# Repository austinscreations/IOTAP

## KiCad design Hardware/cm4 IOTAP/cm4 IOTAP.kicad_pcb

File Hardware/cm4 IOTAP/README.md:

kicad files
=====================

These kicad files are of the orginal design done by jon oxer.

I (austins_creations) got excited about a cm4 design. so put together this schematic
that should be all the needed elements to make the cm4 wifi IOT AP project work.
added the DIY POE switcher
added the ability for the cm4 to know which power mode is in use

pcb veiw is left mostly blank for jon to do routing on stream (if he so chooses to use the files)
but pcb veiw does have the elements from the last design copies over and converted for kicad use to ensure DRC passes

Credits
-------
 * Jonathan Oxer <jon@oxer.com.au>
 * Tony Smith
 * Austin's Creations <https://www.austinscreations.ca/>
 * All the folks watching and commenting on the streams!

License
-------
Copyright 2020-2022 SuperHouse Automation Pty Ltd  www.superhouse.tv  

The hardware portion of this project is licensed under the TAPR Open
Hardware License (www.tapr.org/OHL). The "license" folder within this
repository contains a copy of this license in plain text format.

The software portion of this project is licensed under the Simplified
BSD License. The "licence" folder within this project contains a
copy of this license in plain text format.

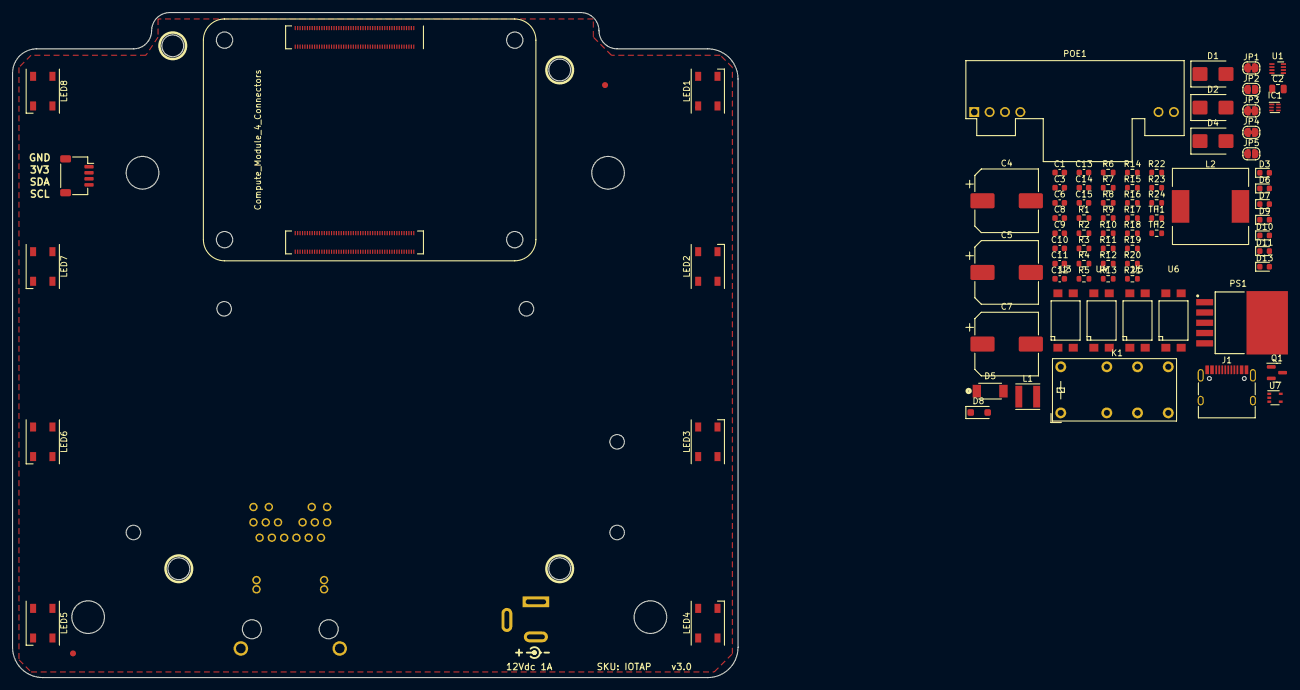
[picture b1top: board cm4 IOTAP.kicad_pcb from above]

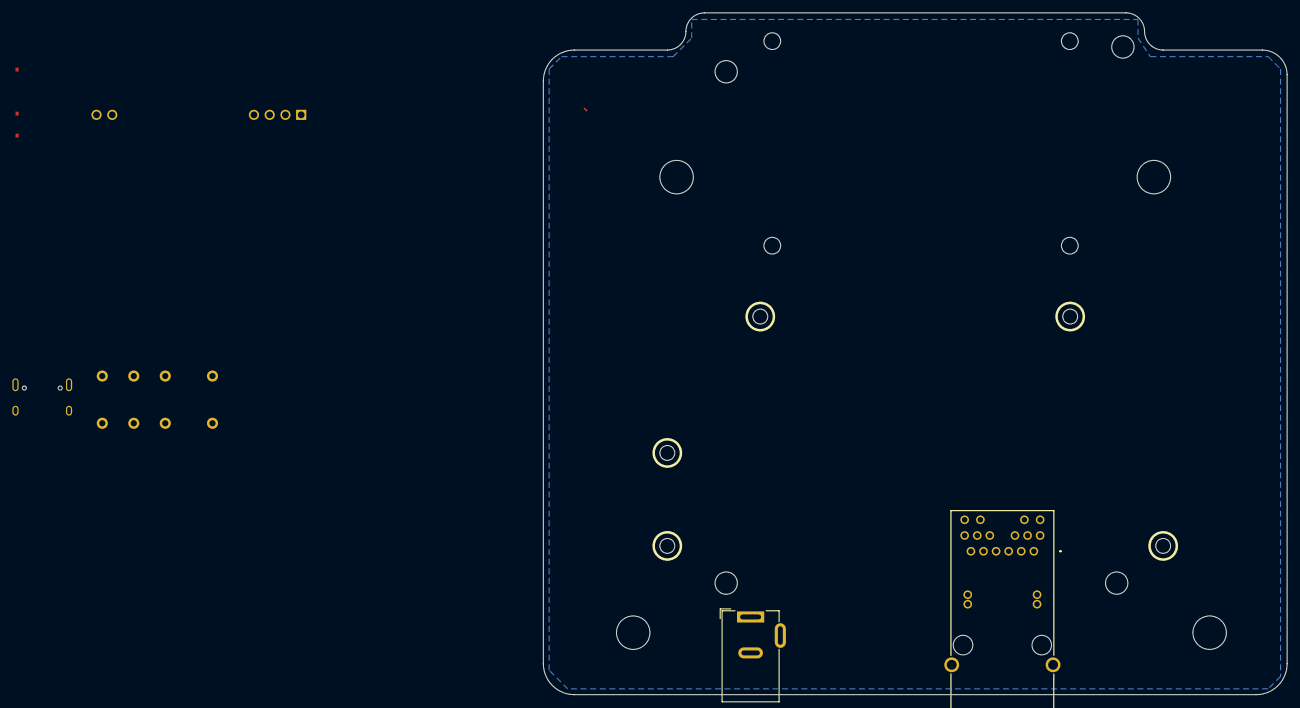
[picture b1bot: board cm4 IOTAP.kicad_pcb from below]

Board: 2 copper layers, 120.0 x 110.0 mm, 99 parts (2 on the bottom side), 72 nets.

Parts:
BJ1: Barrel_Jack; Barrel Jack
C1, C8, C9, C10, C11, C12, C13, C14, C15: 100nF; C_0603_1608Metric
C2: 1uf; C_0805_2012Metric
C3: 1uf; C_0603_1608Metric
C4, C5: 330uF 50v; CP_Elec_10x10
C6: 10uf; C_0603_1608Metric
C7: 330uF 25v; CP_Elec_10x10
D1, D2, D4: S3MB; D_SMB
D3, D10, D11: green; LED_0603_1608Metric
D5: PMEG4050EP; PMEG3050EP
D6, D9, D13: red; LED_0603_1608Metric
D7: blue; LED_0603_1608Metric
D8: SM4007; D_SOD-123F
FID1, FID2: Fiducial; Fiducial_1mm_Mask3mm
H1, H2, H3, H4, H5: MountingHole; MountingHole_2.5mm
H6, H7, H8, H9: MountingHole; MountingHole_3.5mm
H10, H11, H12, H13: MountingHole; MountingHole_5.3mm_M5
IC1: TPS3700-WSON; WSON-6_1.5x1.5mm_P0.5mm
J1: USB_C_Receptacle_USB2.0; USB_C_Receptacle_HRO_TYPE-C-31-M-12
JP1, JP3, JP4: Jumper_2_Bridged; SolderJumper-2_P1.3mm_Bridged_RoundedPad1.0x1.5mm
JP2: Jumper_2_Open; SolderJumper-2_P1.3mm_Open_RoundedPad1.0x1.5mm
JP5: USB OTG MODE; SolderJumper-2_P1.3mm_Open_RoundedPad1.0x1.5mm
K1: J104D2C3VDC.15S; Relay_DPDT_Finder_30.22
L1: 33UH; L_Vishay_IFSC-1515AH_4x4x1.8mm
L2: 33UH; 12x12x8 inductor
LED1, LED2, LED3, LED4, LED5, LED6, LED7, LED8: SK6812; LED_SK6812_PLCC4_5.0x5.0mm_P3.2mm
POE1: DP1435
PS1: LM2596S-5.0; LM2596S
Q1: AO3400A; SOT-23
Qw1: qwiic_horizontal; qwiic horizontal
R1, R2, R3, R8, R12, R13, R14, R16, R17, R18, R19: 10k; R_0603_1608Metric
R4: 2M; R_0603_1608Metric
R5: 62k; R_0603_1608Metric
R6: 22k; R_0603_1608Metric
R7, R9, R10, R15: 4.7k; R_0603_1608Metric
R11, R23, R24: 470r; R_0603_1608Metric
R20, R22: 2.2k; R_0603_1608Metric
R21: 1k; R_0603_1608Metric
RJ45_1: ARJ-139; ARJ139
TH1, TH2: 16v 500mA PTC; R_0603_1608Metric
U1: MAX15062A; DFN-8_2x2mm_P0.5mm
U2: Compute_Module_4_Connectors; Raspberry-Pi-4-Compute-Module
U3, U4, U5, U6: PC817; smd4
U7: 74LVC1G07SE-7; SOT-353_SC-70-5

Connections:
2.1mm_SIG: BJ1.1, D2.1 (K), D10.2 (A), R12.2
+1V8: JP2.1 (A), TH1.1
+3.3V: D9.2 (A), D13.2 (A), JP1.1 (A), Qw1.2 (VCC), R16.1, R17.1, R18.1, R19.1, RJ45_1.18 (A_YELLOW), RJ45_1.20 (K_ORANGE/A_GREEN), TH2.1, U7.5 (VCC)
+3.3VA: C6.1, D7.2 (A), D8.1 (K), IC1.2 (VDD), L1.2, R8.1, R15.2, U1.4 (FB/Vout)
+5V: C7.1, C8.2, C9.2, C10.2, C11.2, C12.2, C13.2, C14.2, C15.2, D6.2 (A), L2.2, LED1.3 (VDD), LED2.3 (VDD), LED3.3 (VDD), LED4.3 (VDD), LED5.3 (VDD), LED6.3 (VDD), LED7.3 (VDD), LED8.3 (VDD), PS1.4 (FB), U2.77 (+5V), U2.79 (+5V), U2.81 (+5V), U2.83 (+5V), U2.85 (+5V), U2.87 (+5V)
+12V: C4.1, C5.1, D1.2 (A), D2.2 (A), D4.2 (A), PS1.1 (VIN)
/nPWR_LED: U2.95 (~PI_LED_nPWR), U7.2
DIY_SIG: D8.2 (A), JP4.2 (B), Q1.3 (D), U6.2
ETH_LEDG: R24.2, U2.17 (~Ethernet_nLED2)
ETH_LEDY: R23.2, U2.15 (~Ethernet_nLED3)
GND: BJ1.2, BJ1.3, C1.2, C4.2, C5.2, C7.2, C8.1, C9.1, C10.1, C11.1, C12.1, C13.1, C14.1, C15.1, D5.2 (A), J1.A1 (GND), J1.A12 (GND), J1.B1 (GND), J1.B12 (GND), J1.S1 (SHIELD), JP3.2 (B), LED1.1 (VSS), LED2.1 (VSS), LED3.1 (VSS), LED4.1 (VSS), LED5.1 (VSS), LED6.1 (VSS), LED7.1 (VSS), LED8.1 (VSS), POE1.GND, PS1.3 (GND), PS1.5 (~ON/OFF), Qw1.1 (GND), Qw1.MP, R22.1, RJ45_1.MH1, RJ45_1.MH2, U2.1 (GND), U2.2 (GND), U2.7 (GND), U2.8 (GND), U2.13 (GND), U2.14 (GND), U2.22 (GND), U2.23 (GND), U2.32 (GND), U2.33 (GND), U2.42 (GND), U2.43 (GND), U2.52 (GND), U2.53 (GND), U2.59 (GND), U2.60 (GND), U2.65 (GND), U2.66 (GND), U2.71 (GND), U2.74 (GND), U2.98 (GND), U2.107 (GND), U2.108 (GND), U2.113 (GND), U2.114 (GND), U2.119 (GND), U2.120 (GND), U2.125 (GND), U2.126 (GND), U2.131 (GND), U2.132 (GND), U2.137 (GND), U2.138 (GND), U2.144 (GND), U2.150 (GND), U2.155 (GND), U2.156 (GND), U2.161 (GND), U2.162 (GND), U2.167 (GND), U2.168 (GND), U2.173 (GND), U2.174 (GND), U2.179 (GND), U2.180 (GND), U2.185 (GND), U2.186 (GND), U2.191 (GND), U2.192 (GND), U2.197 (GND), U2.198 (GND), U3.2, U3.3, U4.2, U4.3, U5.2, U5.3, U6.3, U7.3 (GND)
GPIO8: R16.2, U2.39 (GPIO8), U3.4
GPIO18: R11.1, U2.49 (GPIO18)
GPIO23: R19.2, U2.47 (GPIO23), U6.4
GPIO24: R18.2, U2.45 (GPIO24), U5.4
GPIO25: R17.2, U2.41 (GPIO25), U4.4
GPIO_VREF: JP1.2 (B), JP2.2 (B), U2.78 (GPIO_VREF)
unnamed: D3.1 (K), R2.1
unnamed: D5.1 (K), L2.1, PS1.2 (OUT)
unnamed: D6.1 (K), R7.1
unnamed: D7.1 (K), R10.1
unnamed: D9.1 (K), R9.1
unnamed: D10.1 (K), R1.1
unnamed: D11.1 (K), R3.1
unnamed: D13.1 (K), R21.1
unnamed: IC1.4 (INA+), R4.2, R5.1
unnamed: IC1.3 (INB-), R5.2, R6.1
unnamed: IC1.1 (OUTB), IC1.6 (OUTA), Q1.1 (G), R8.2
unnamed: JP3.1 (A), R1.2, R2.2, R3.2, R7.2
unnamed: JP4.1 (A), R10.2
unnamed: JP5.1 (A), R20.1
unnamed: J1.A4 (VBUS), J1.A9 (VBUS), J1.B4 (VBUS), J1.B9 (VBUS), JP5.2 (B)
unnamed: LED1.2 (DIN), R11.2
unnamed: LED1.4 (DOUT), LED2.2 (DIN)
unnamed: LED2.4 (DOUT), LED3.2 (DIN)
unnamed: LED3.4 (DOUT), LED4.2 (DIN)
unnamed: LED4.4 (DOUT), LED5.2 (DIN)
unnamed: LED5.4 (DOUT), LED6.2 (DIN)
unnamed: LED6.4 (DOUT), LED7.2 (DIN)
unnamed: LED7.4 (DOUT), LED8.2 (DIN)
unnamed: R12.1, U3.1
unnamed: R13.1, U4.1
unnamed: R14.1, U5.1
unnamed: R15.1, U6.1
unnamed: R21.2, U7.4
unnamed: C1.1, RJ45_1.1 (CT_1), RJ45_1.6 (CT_2), RJ45_1.7 (CT_3), RJ45_1.12 (CT_4)
unnamed: R24.1, RJ45_1.19 (K_GREEN/A_ORANGE)
unnamed: R23.1, RJ45_1.17 (K_YELLOW)
unnamed: TH1.2, U2.88 (CM4_1.8V_Out), U2.90 (CM4_1.8V_Out)
unnamed: TH2.2, U2.84 (CM4_3.3V_Out), U2.86 (CM4_3.3V_Out)
unnamed: L1.1, U1.8 (LX)
unnamed: C3.1, U1.3 (VCC)
unnamed: R9.2, U2.21 (~Pi_nLED_Activity)
PASSIVE_SIG: D1.1 (K), D11.2 (A), R14.2
POE_SIG: D3.2 (A), D4.1 (K), POE1.VOUT, R13.2
SCL0: Qw1.4 (SCL), U2.80 (I2C_SCL0)
SDA0: Qw1.3 (SDA), U2.82 (I2C_SDA0)
USB2_N: J1.A7 (D-), J1.B7 (D-), U2.103 (USB_N)
USB2_P: J1.A6 (D+), J1.B6 (D+), U2.105 (USB_P)
USBOTG: R20.2, R22.2, U2.101 (USB_OTG_ID)
VA1: POE1.VA1, RJ45_1.13 (POE_1)
VA2: POE1.VA2, RJ45_1.14 (POE_2)
VB1: C2.1, R4.1, RJ45_1.15 (POE_3), U1.1 (VIN), U1.2 (EN/UVLO)
VB2: C2.2, C3.2, C6.2, IC1.5 (GND), Q1.2 (S), R6.2, RJ45_1.16 (POE_4), U1.5 (MODE), U1.7 (GND)
ethPair0_N: RJ45_1.10 (TRD0-), U2.10 (Ethernet_Pair0_N)
ethPair0_P: RJ45_1.11 (TRD0+), U2.12 (Ethernet_Pair0_P)
ethPair1_N: RJ45_1.5 (TRD1-), U2.6 (Ethernet_Pair1_N)
ethPair1_P: RJ45_1.4 (TRD1+), U2.4 (Ethernet_Pair1_P)
ethPair2_N: RJ45_1.2 (TRD2-), U2.9 (Ethernet_Pair2_N)
ethPair2_P: RJ45_1.3 (TRD2+), U2.11 (Ethernet_Pair2_P)
ethPair3_N: RJ45_1.9 (TRD3-), U2.5 (Ethernet_Pair3_N)
ethPair3_P: RJ45_1.8 (TRD3+), U2.3 (Ethernet_Pair3_P)

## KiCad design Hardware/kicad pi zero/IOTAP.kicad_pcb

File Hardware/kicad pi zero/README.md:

kicad files
=====================

These kicad files are of the orginal design done by jon oxer.

I (austins_creations) imported these to kicad to get the general pcb layout for a CM4 design

Credits
-------
 * Jonathan Oxer <jon@oxer.com.au>
 * Tony Smith
 * Austin's Creations <https://www.austinscreations.ca/>
 * All the folks watching and commenting on the streams!

License
-------
Copyright 2020-2022 SuperHouse Automation Pty Ltd  www.superhouse.tv  

The hardware portion of this project is licensed under the TAPR Open
Hardware License (www.tapr.org/OHL). The "license" folder within this
repository contains a copy of this license in plain text format.

The software portion of this project is licensed under the Simplified
BSD License. The "licence" folder within this project contains a
copy of this license in plain text format.

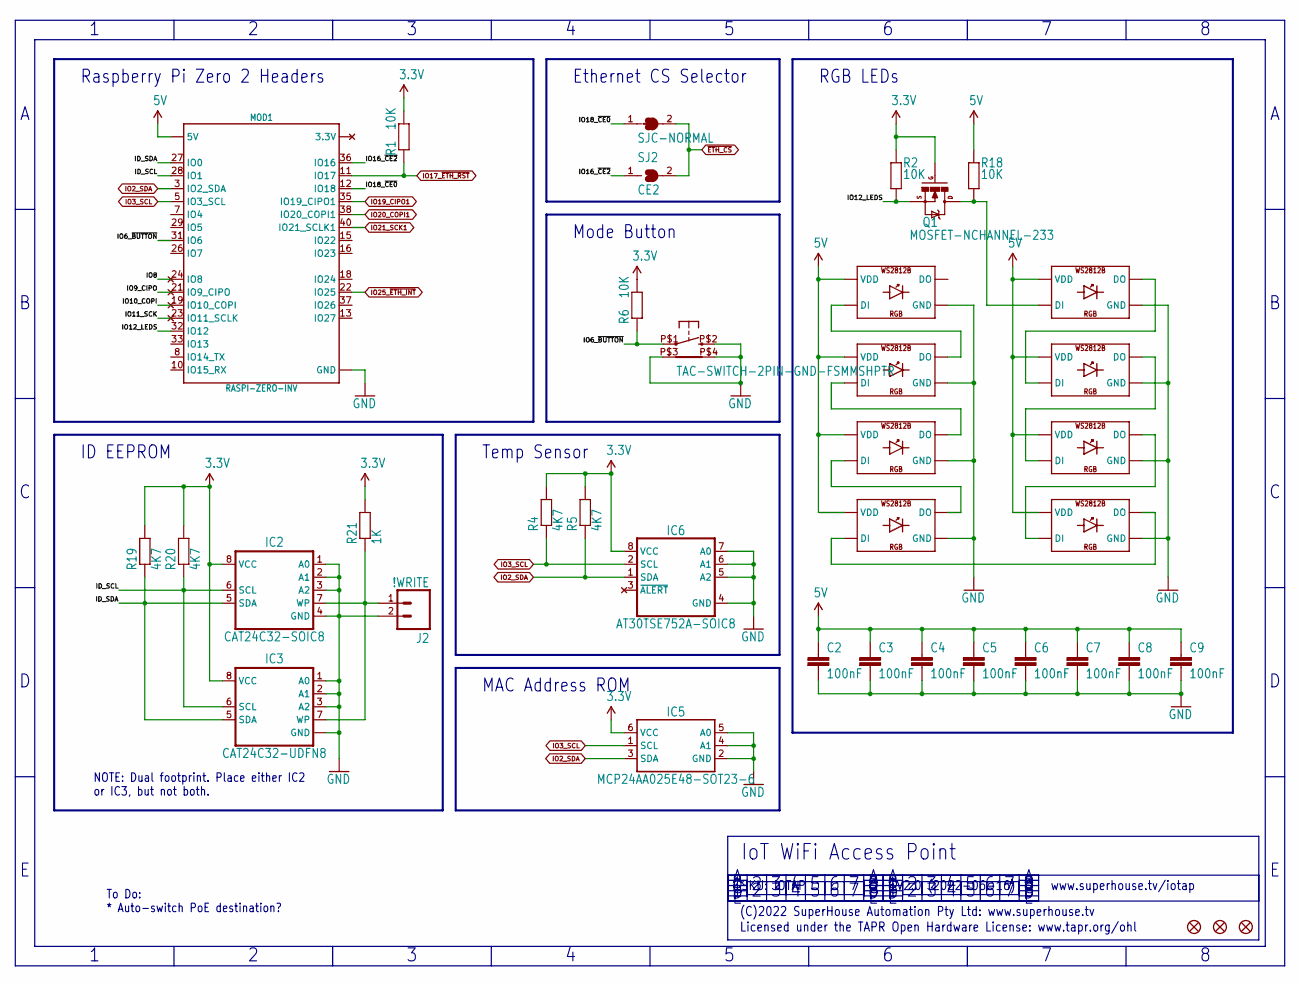
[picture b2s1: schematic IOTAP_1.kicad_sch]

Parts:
C2, C3, C4, C5, C6, C7, C8, C9: 100nF; C0603
FID1, FID2, FID3: FIDUCIAL1X2.5; FIDUCIAL-1X2.5
IC2: CAT24C32-SOIC8; SOIC8
IC3: CAT24C32-UDFN8; UDFN8
IC5: MCP24AA025E48-SOT23-6; SOT23-6
IC6: AT30TSE752A-SOIC8; SOIC8
J2: !WRITE; 1X02
LED1, LED2, LED3, LED4, LED5, LED6, LED7, LED8: WS2812B5050; WS2812B
MOD1: RASPI-ZERO-INV; RPI-ZERO-INV
Q1: MOSFET-NCHANNEL-233; SOT23-3
R1, R2, R6, R18: 10K; R0603
R4, R5, R19, R20: 4K7; R0603
R21: 1K; R0603
SJ1: SJC-NORMAL; SJC
SJ2: CE2; SJ
SW1: TAC-SWITCH-2PIN-GND-FSMMSHPTR; TC-120V

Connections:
3.3V: IC2.8 (VCC), IC3.8 (VCC), IC5.6 (VCC), IC6.8 (VCC), Q1.1 (G), R1.2, R2.2, R4.2, R5.2, R6.2, R19.2, R20.2, R21.2; also elsewhere on the board
5V: C2.1, C3.1, C4.1, C5.1, C6.1, C7.1, C8.1, C9.1, LED1.1-VDD (VDD), LED2.1-VDD (VDD), LED3.1-VDD (VDD), LED4.1-VDD (VDD), LED5.1-VDD (VDD), LED6.1-VDD (VDD), LED7.1-VDD (VDD), LED8.1-VDD (VDD), MOD1.2 (5V), MOD1.4 (5V), R18.2; also elsewhere on the board
GND: C2.2, C3.2, C4.2, C5.2, C6.2, C7.2, C8.2, C9.2, IC2.1 (A0), IC2.2 (A1), IC2.3 (A2), IC2.4 (GND), IC3.1 (A0), IC3.2 (A1), IC3.3 (A2), IC3.4 (GND), IC3.PAD (GND), IC5.2 (GND), IC5.4 (A1), IC5.5 (A0), IC6.4 (GND), IC6.5 (A2), IC6.6 (A1), IC6.7 (A0), J2.2, LED1.3-GND (GND), LED2.3-GND (GND), LED3.3-GND (GND), LED4.3-GND (GND), LED5.3-GND (GND), LED6.3-GND (GND), LED7.3-GND (GND), LED8.3-GND (GND), MOD1.6 (GND), MOD1.9 (GND), MOD1.14 (GND), MOD1.20 (GND), MOD1.25 (GND), MOD1.30 (GND), MOD1.34 (GND), MOD1.39 (GND), SW1.P$2 (2), SW1.P$3 (TAB1), SW1.P$4 (TAB2); also elsewhere on the board
ID_SCL: IC2.6 (SCL), IC3.6 (SCL), MOD1.28 (IO1), R20.1
ID_SDA: IC2.5 (SDA), IC3.5 (SDA), MOD1.27 (IO0), R19.1
IO2_SDA: IC5.3 (SDA), IC6.1 (SDA), MOD1.3 (IO2_SDA), R5.1; also elsewhere on the board
IO3_SCL: IC5.1 (SCL), IC6.2 (SCL), MOD1.5 (IO3_SCL), R4.1; also elsewhere on the board
IO6_~BUTTON: MOD1.31 (IO6), R6.1, SW1.P$1 (1)
IO8: MOD1.24 (IO8)
IO9_CIPO: MOD1.21 (IO9_CIPO)
IO10_COPI: MOD1.19 (IO10_COPI)
IO11_SCK: MOD1.23 (IO11_SCLK)
IO12_LEDS: MOD1.32 (IO12), Q1.2 (S), R2.1
IO16_~CE2: MOD1.36 (IO16), SJ2.1
IO17_~ETH_RST: MOD1.11 (IO17), R1.1; also elsewhere on the board
IO18_~CE0: MOD1.12 (IO18), SJ1.1
IO19_CIPO1: MOD1.35 (IO19_CIPO1); also elsewhere on the board
IO20_COPI1: MOD1.38 (IO20_COPI1); also elsewhere on the board
IO21_SCK1: MOD1.40 (IO21_SCLK1); also elsewhere on the board
IO25_~ETH_INT: MOD1.22 (IO25); also elsewhere on the board
LEDS: LED1.4-DIN (DI), Q1.3 (D), R18.1
unnamed: IC2.7 (WP), IC3.7 (WP), J2.1, R21.1
unnamed: LED4.2-DOUT (DO), LED5.4-DIN (DI)
unnamed: LED5.2-DOUT (DO), LED6.4-DIN (DI)
unnamed: LED6.2-DOUT (DO), LED7.4-DIN (DI)
unnamed: LED7.2-DOUT (DO), LED8.4-DIN (DI)
unnamed: LED1.2-DOUT (DO), LED2.4-DIN (DI)
unnamed: LED2.2-DOUT (DO), LED3.4-DIN (DI)
unnamed: LED3.2-DOUT (DO), LED4.4-DIN (DI)
~ETH_CS: SJ1.2, SJ2.2; also elsewhere on the board

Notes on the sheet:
RGB LEDs
ID EEPROM
(C)2022 SuperHouse Automation Pty Ltd: www.superhouse.tv
MAC Address ROM
SKU: IOTAP
NOTE: Dual footprint. Place either IC2 or IC3, but not both.
To Do: * Auto-switch PoE destination?
Temp Sensor
Licensed under the TAPR Open Hardware License: www.tapr.org/ohl
Mode Button
Ethernet CS Selector
IoT WiFi Access Point
www.superhouse.tv/iotap
V2.0 (2022-06-16)
Raspberry Pi Zero 2 Headers

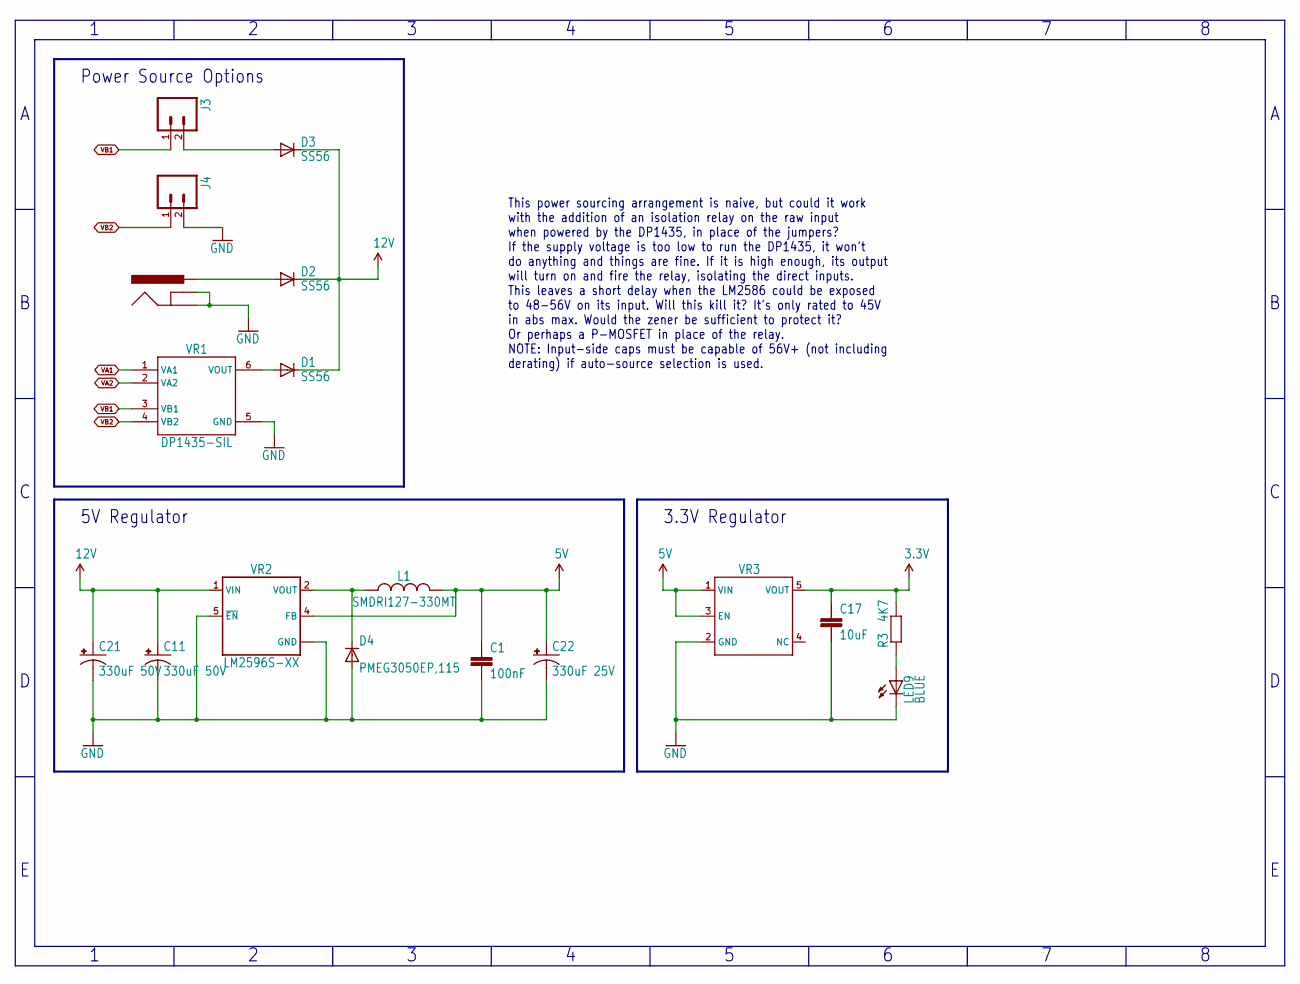
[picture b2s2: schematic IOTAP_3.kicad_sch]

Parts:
C1: 100nF; C0603
C11, C21: 330uF 50V; PANASONIC_G
C17: 10uF; C0805
C22: 330uF 25V; PANASONIC_G
D1, D2, D3: SS56; SMA-DIODE
D4: PMEG3050EP,115; SOD-128
J1: POWER_JACK-SLOTS; POWER_JACK_SLOTS
J3, J4: M02-PIN-RA; 1X02-P-RA
L1: SMDRI127-330MT; INDPM120120X800N
LED9: BLUE; LED-0603
R3: 4K7; R0603
VR1: DP1435-SIL; DP1435
VR2: LM2596S-XX; TO170P1435X465-6N
VR3: AP2112KSOT25; SOT23-5

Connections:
3.3V: C17.1, R3.2, VR3.5 (VOUT); also elsewhere on the board
5V: C1.1, C22.+, L1.2, VR2.4 (FB), VR3.1 (VIN), VR3.3 (EN); also elsewhere on the board
12V: C11.+, C21.+, D1.C, D2.C, D3.C, VR2.1 (VIN)
GND: C1.2, C11.-, C17.2, C21.-, C22.-, D4.2 (A), J1.GND, J1.GNDBREAK, J4.2, LED9.C, VR1.5 (GND), VR2.3 (GND), VR2.5 (~EN), VR2.6 (GND), VR3.2 (GND); also elsewhere on the board
unnamed: D3.A, J3.2
unnamed: D4.1 (C), L1.1, VR2.2 (VOUT)
unnamed: LED9.A, R3.1
unnamed: D2.A, J1.PWR
unnamed: D1.A, VR1.6 (VOUT)
VA1: VR1.1 (VA1); also elsewhere on the board
VA2: VR1.2 (VA2); also elsewhere on the board
VB1: J3.1, VR1.3 (VB1); also elsewhere on the board
VB2: J4.1, VR1.4 (VB2); also elsewhere on the board

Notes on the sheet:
This power sourcing arrangement is naive, but could it work with the addition of an isolation relay on the raw input when powered by the DP1435, in place of the jumpers? If the supply voltage is too low to run the DP1435, it won't do anything and things are fine. If it is high enough, its output wi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
5V Regulator
Power Source Options
3.3V Regulator

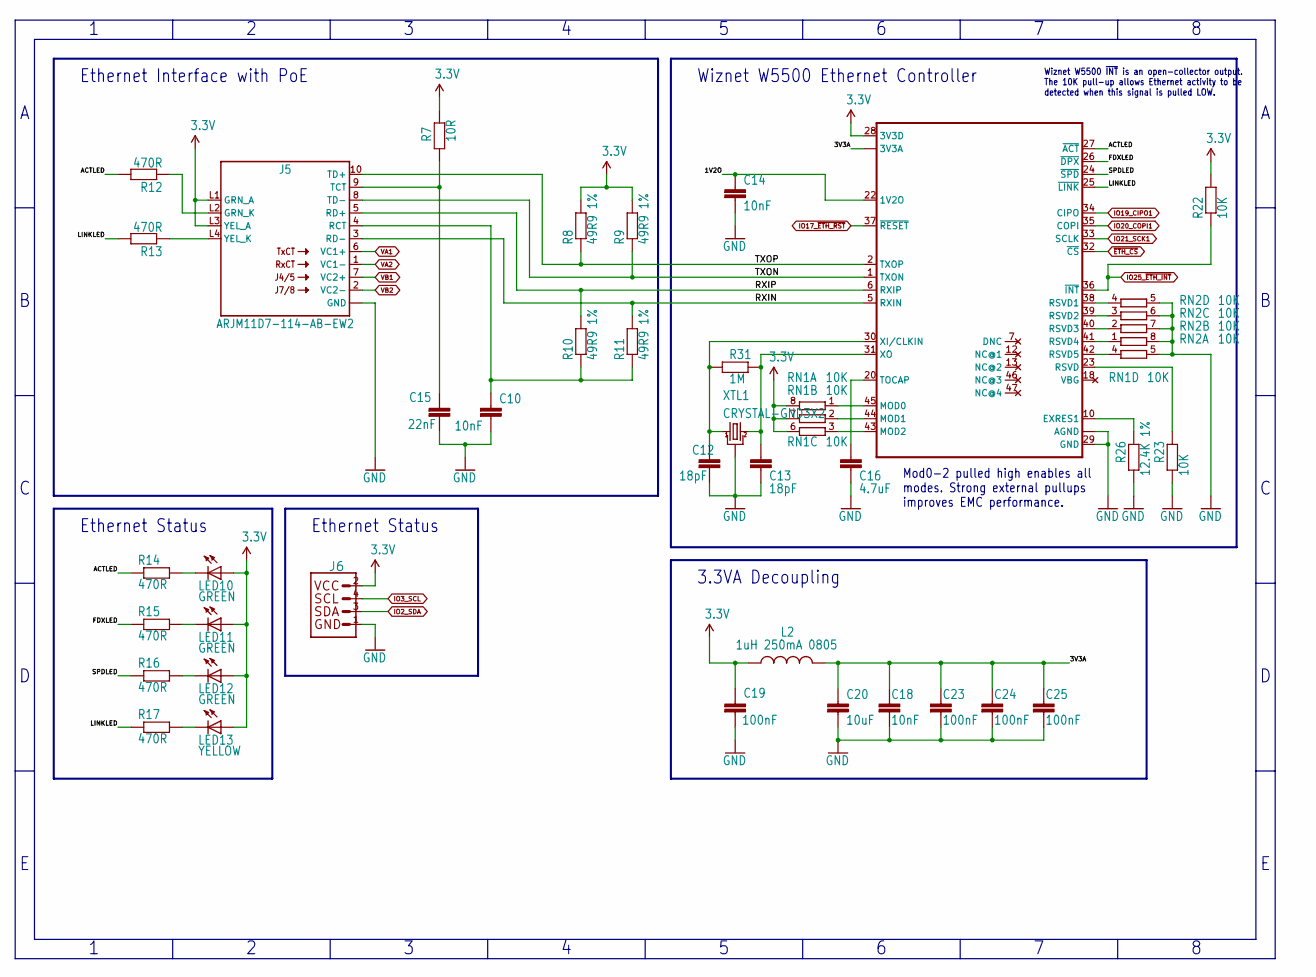
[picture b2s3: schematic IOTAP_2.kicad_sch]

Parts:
C10, C14, C18: 10nF; C0603
C12, C13: 18pF; C0603
C15: 22nF; C0603
C16: 4.7uF; C0603
C19, C23, C24, C25: 100nF; C0603
C20: 10uF; C0805
IC4: W5500-LQFP; LQFP48
J5: ARJM11D7-114-AB-EW2; ARJM11D7114ABEW2
J6: QWIICJS-1MM; 1X04_QWIIC_1MM_RA
L2: 1uH 250mA 0805; L2012C
LED10, LED11, LED12: GREEN; LED-0603
LED13: YELLOW; LED-0603
R7: 10R; R0603
R8, R9, R10, R11: 49R9 1%; R0603
R12, R13, R14, R15, R16, R17: 470R; R0603
R22, R23: 10K; R0603
R26: 12.4K 1%; R0603
R31: 1M; R0603
RN1, RN2: 10K; CAY16
XTL1: CRYSTAL-GND3X2; CRYSTAL-SMD-3X2

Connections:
1V2O: C14.1, IC4.22 (1V2O)
3.3V: C19.1, IC4.28 (3V3D), J5.L1 (GRN_A), J5.L3 (YEL_A), J6.2, L2.1, LED10.A, LED11.A, LED12.A, LED13.A, R7.1, R8.2, R9.2, R22.2, RN1.6 (2), RN1.7 (2), RN1.8 (2); also elsewhere on the board
3V3A: C18.1, C20.1, C23.1, C24.1, C25.1, IC4.4 (3V3A), IC4.8 (3V3A), IC4.11 (3V3A), IC4.15 (3V3A), IC4.17 (3V3A), IC4.21 (3V3A), L2.2
ACTLED: IC4.27 (~ACT), R12.2, R14.1
FDXLED: IC4.26 (~DPX), R15.1
GND: C10.2, C12.2, C13.2, C14.2, C15.2, C16.2, C18.2, C19.2, C20.2, C23.2, C24.2, C25.2, IC4.3 (AGND), IC4.9 (AGND), IC4.14 (AGND), IC4.16 (AGND), IC4.19 (AGND), IC4.29 (GND), IC4.48 (AGND), J5.MH1 (GND), J5.MH2 (GND), J6.1, R23.2, R26.2, RN1.5 (2), RN2.5 (2), RN2.6 (2), RN2.7 (2), RN2.8 (2), XTL1.2 (GND), XTL1.4 (GND); also elsewhere on the board
IO2_SDA: J6.3; also elsewhere on the board
IO3_SCL: J6.4; also elsewhere on the board
IO17_~ETH_RST: IC4.37 (~RESET); also elsewhere on the board
IO19_CIPO1: IC4.34 (CIPO); also elsewhere on the board
IO20_COPI1: IC4.35 (COPI); also elsewhere on the board
IO21_SCK1: IC4.33 (SCLK); also elsewhere on the board
IO25_~ETH_INT: IC4.36 (~INT), R22.1; also elsewhere on the board
LINKLED: IC4.25 (~LINK), R13.2, R17.1
unnamed: J5.L4 (YEL_K), R13.1
unnamed: J5.L2 (GRN_K), R12.1
unnamed: C13.1, IC4.31 (XO), R31.1, XTL1.3 (2)
unnamed: C10.1, J5.4 (RCT), R10.1, R11.1
unnamed: LED12.C, R16.2
unnamed: C12.1, IC4.30 (XI/CLKIN), R31.2, XTL1.1
unnamed: LED13.C, R17.2
unnamed: C16.1, IC4.20 (TOCAP)
unnamed: C15.1, J5.9 (TCT), R7.2
unnamed: IC4.10 (EXRES1), R26.1
unnamed: IC4.23 (RSVD), R23.1
unnamed: IC4.45 (MOD0), RN1.1
unnamed: IC4.44 (MOD1), RN1.2 (1)
unnamed: IC4.43 (MOD2), RN1.3 (1)
unnamed: IC4.42 (RSVD5), RN1.4 (1)
unnamed: IC4.41 (RSVD4), RN2.1
unnamed: IC4.40 (RSVD3), RN2.2 (1)
unnamed: IC4.39 (RSVD2), RN2.3 (1)
unnamed: IC4.38 (RSVD1), RN2.4 (1)
unnamed: LED11.C, R15.2
unnamed: LED10.C, R14.2
RXIN: IC4.5 (RXIN), J5.3 (RD-), R11.2
RXIP: IC4.6 (RXIP), J5.5 (RD+), R10.2
SPDLED: IC4.24 (~SPD), R16.1
TXON: IC4.1 (TXON), J5.8 (TD-), R9.1
TXOP: IC4.2 (TXOP), J5.10 (TD+), R8.1
VA1: J5.6 (VC1+); also elsewhere on the board
VA2: J5.1 (VC1-); also elsewhere on the board
VB1: J5.7 (VC2+); also elsewhere on the board
VB2: J5.2 (VC2-); also elsewhere on the board
~ETH_CS: IC4.32 (~CS); also elsewhere on the board

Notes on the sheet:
Ethernet Interface with PoE
3.3VA Decoupling
Ethernet Status
Wiznet W5500 ~{INT} is an open-collector output. The 10K pull-up allows Ethernet activity to be detected when this signal is pulled LOW.
Mod0-2 pulled high enables all modes. Strong external pullups improves EMC performance.
Wiznet W5500 Ethernet Controller

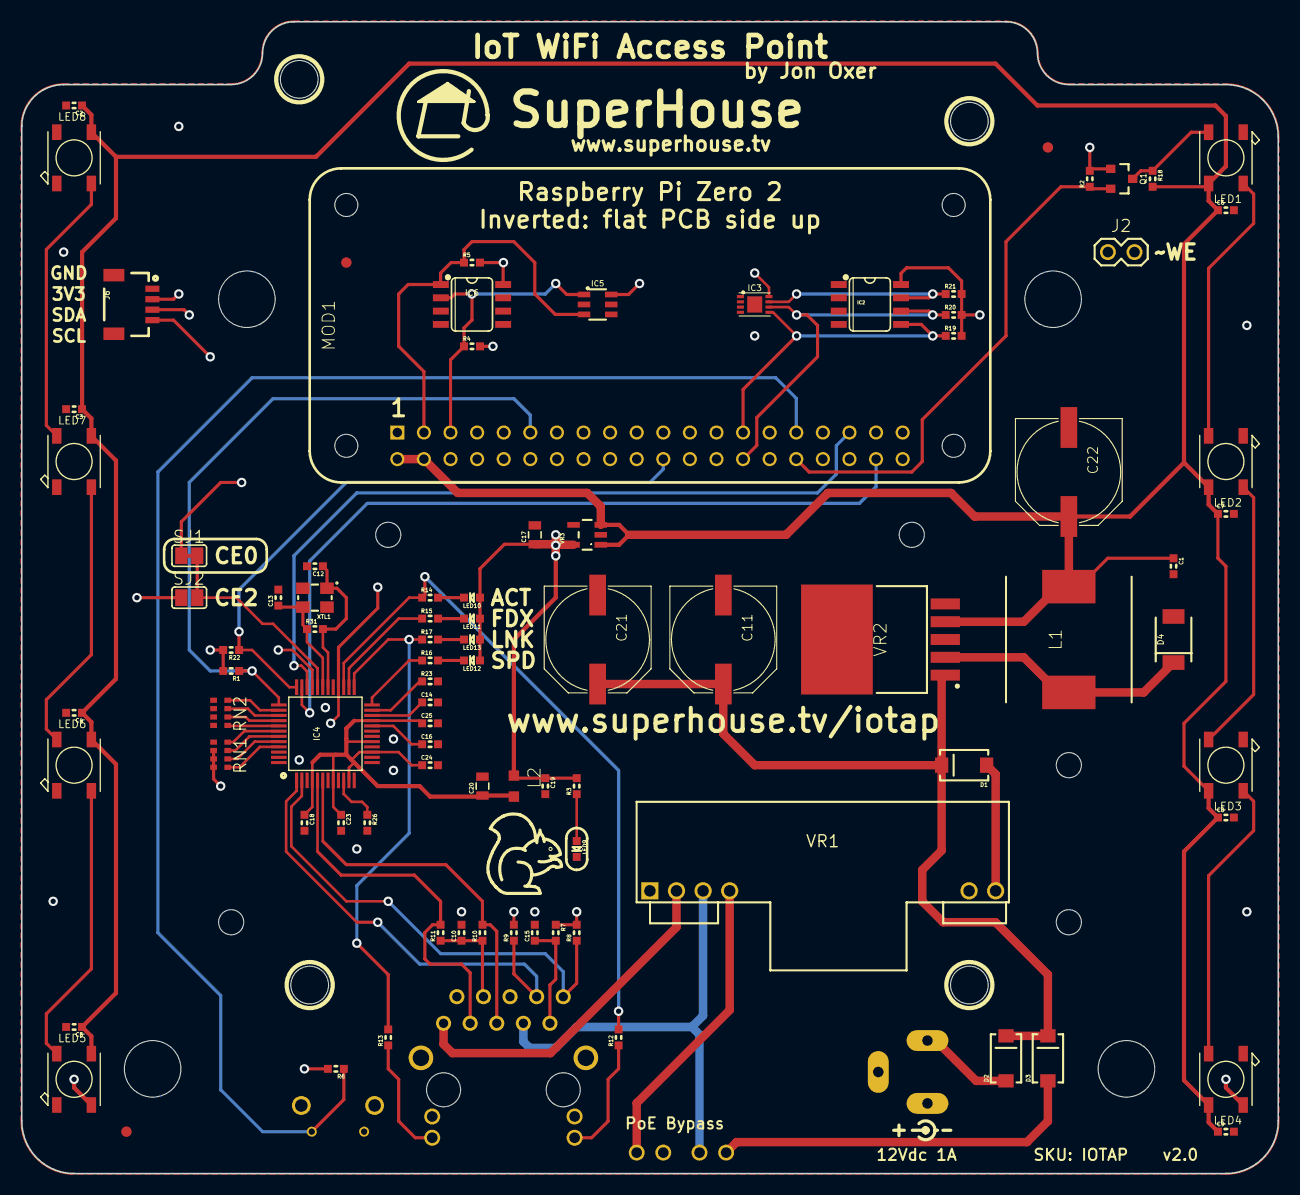
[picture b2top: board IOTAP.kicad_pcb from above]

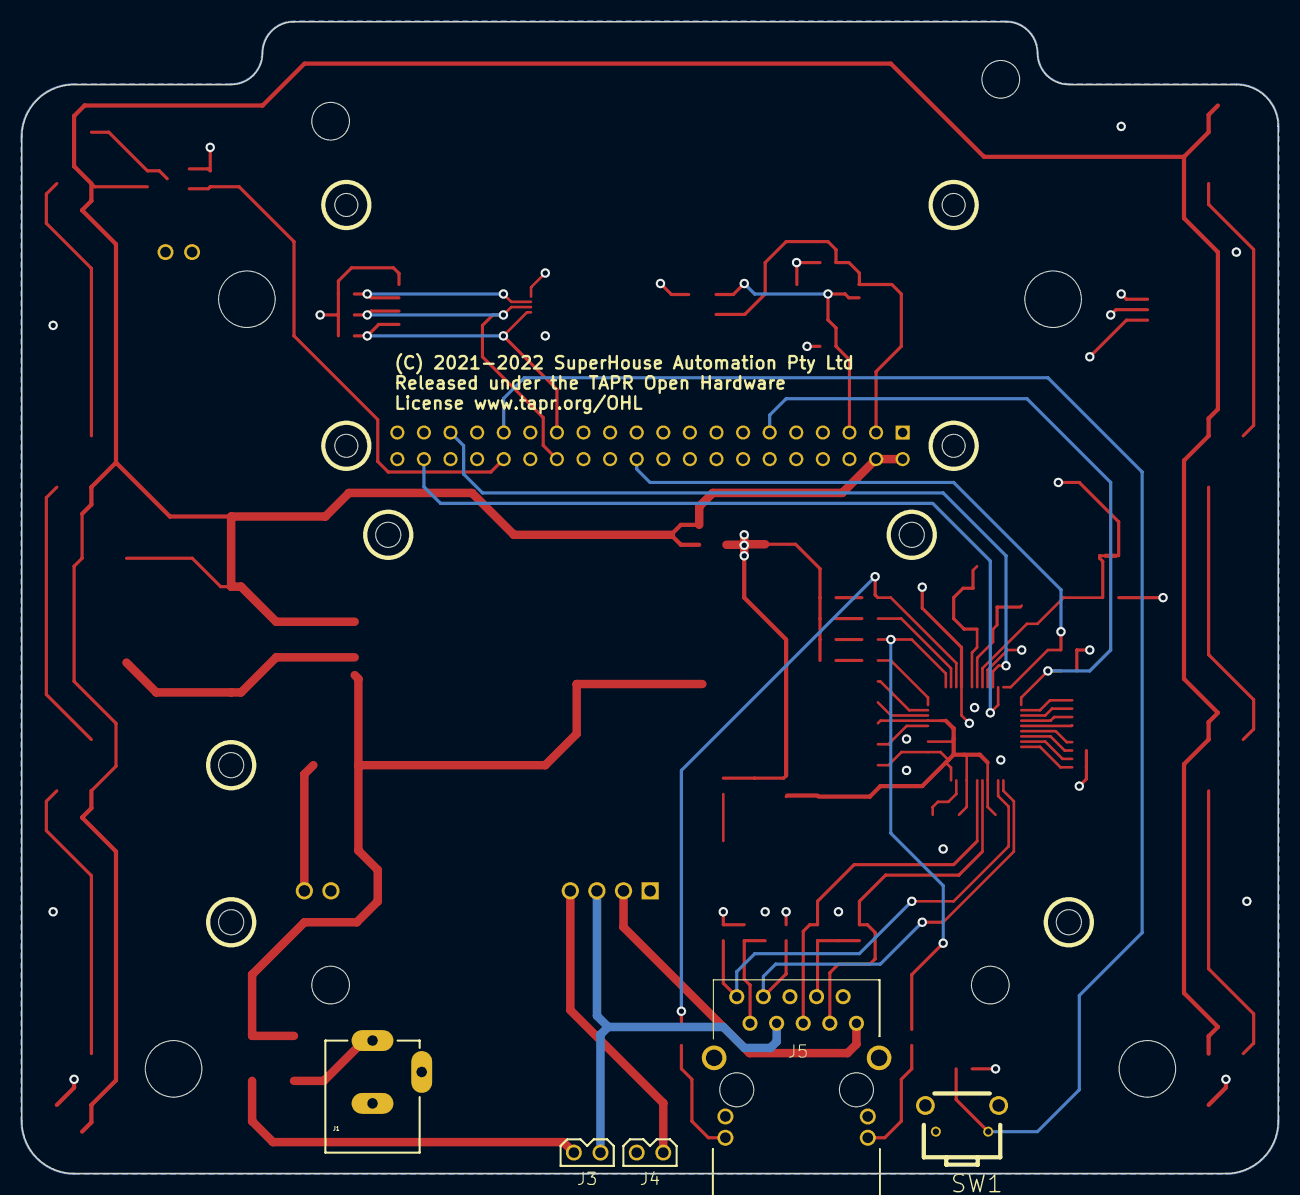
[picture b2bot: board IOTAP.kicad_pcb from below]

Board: 4 copper layers, 120.0 x 110.0 mm, 107 parts (5 on the bottom side), 67 nets.

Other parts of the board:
@HOLE0, @HOLE1, @HOLE2, @HOLE3, @HOLE4, @HOLE5, @HOLE6, @HOLE7, @HOLE8, @HOLE9, @HOLE10, @HOLE11, @HOLE12: (no value)

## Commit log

2023-10-08 add converted kicad files
2023-10-08 add cm4 design
2023-10-08 Delete Hardware/cm4 IOTAP/cm4 IOTAP-backups directory
    backups aren't needed here
2023-10-08 add resistors for Ethernet activity lights
2023-10-08 add schematic as an image

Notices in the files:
Hardware/kicad pi zero/IOTAP.kicad_pcb:
(C) 2021-2022 SuperHouse Automation Pty Ltd
